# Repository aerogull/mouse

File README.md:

# beat - a mouse designed for any case
I've wanted to design my own mouse for the longest time. I've built my own keyboard, so it was just the next logical step, right? Well, the complexity from a keyboard run off a microcontroller powered by qmk, to a custom programmed mouse with a proprietary mouse sensor and a nRF52 chip, was quite the leap. This is a v1, it's not going to be light, it's not going to be very small, the side button connectors will likely be changed, and the case will not be ergonomic in any way that isn't comfortable to me. The firmware will be slower than most modern mice, and I probably won't be able to bring out the full speed of the PAW3395 sensor used (if I use ESB). But this is a testing board, and changes will be made to improve it in the future! With that, onto the specs and design!
## PCB
- nRF52840
- PAW3395
- 11mm compatible Alps scroll (w middle click)
- 4 Omron Switches (1 other switch for middle click)
- Lipo battery (500mAH)
- Dongle (nRF52840 + USBC) (COMING SOON)
- USBC charging

## Case
## Firmware
_**Warning: The PAW3395 Driver is Propiretiary, and Can Not Be Provided by Me**_ 

### BOM
|Reference|Qty|Value|DNP|Exclude from BOM|Exclude from Board|Footprint|Datasheet|
|-----|-----|-----|-----|-----|-----|-----|-----|
|A1|1|~||||custom:PAW3395||
|C1,C29,C39|	3|	4.7μF|	|	|	|	Capacitor_SMD:C_0805_2012Metric_Pad1.18x1.45mm_HandSolder|	~|
|C2,C4,C5,C13,C14,C19,C20,C21,C22,C23,C28,C31,C38|	13|	100nF|	|	|	|	Capacitor_SMD:C_0805_2012Metric_Pad1.18x1.45mm_HandSolder|	~|
|C3,C6,C8,C10,C12,C15,C16,C18,C41,C43|	10|	10μF|	|	|	|	Capacitor_SMD:C_0805_2012Metric_Pad1.18x1.45mm_HandSolder|	~|
|C7|	1|	33uF|	|	|	|	Capacitor_SMD:C_0805_2012Metric_Pad1.18x1.45mm_HandSolder|	~|
|C11,C17,C42|	3|	1μF|	|	|	|	Capacitor_SMD:C_0805_2012Metric_Pad1.18x1.45mm_HandSolder|	~|
|C24,C25,C26,C27|	4|	12pF|	|	|	|	Capacitor_SMD:C_0805_2012Metric_Pad1.18x1.45mm_HandSolder|	~|
|C30,C32|	2|	1.0μF|	|	|	|	Capacitor_SMD:C_0805_2012Metric_Pad1.18x1.45mm_HandSolder|	~|
|C33,C37|	2|	N.C.|	|	|	|	Capacitor_SMD:C_0805_2012Metric_Pad1.18x1.45mm_HandSolder|	~|
|C34|	1|	100pF|	|	|	|	Capacitor_SMD:C_0805_2012Metric_Pad1.18x1.45mm_HandSolder|	~|
|C35|	1|	0.8pF|	|	|	|	Capacitor_SMD:C_0805_2012Metric_Pad1.18x1.45mm_HandSolder|	~|
|C36|	1|	0.5pF|	|	|	|	Capacitor_SMD:C_0805_2012Metric_Pad1.18x1.45mm_HandSolder|	~|
|D3,D5|	2|	MBR1020VL|	|	|	|	Diode_SMD:D_SOD-123F|	https://www.onsemi.com/pub/Collateral/MBR1020VL-D.PDF|
|J2|	1|	JSTPH|	|	|	|	custom:JSTPH2PINSMTRIGHTANGLECONNECTOR|	~|
|J3|	1|	USB_C_Receptacle_USB2.0_14P|	|	|	|	Connector_USB:USB_C_Receptacle_Amphenol_12401548E4-2A|	https://www.usb.org/sites/default/files/documents/usb_type-c.zip|
|L1,L4|	2|	10μH|	|	|	|	Inductor_SMD:L_0805_2012Metric_Pad1.05x1.20mm_HandSolder|	~|
|L2|	1|	15nH|	|	|	|	Inductor_SMD:L_0805_2012Metric_Pad1.05x1.20mm_HandSolder|	~|
|L3|	1|	3.3nH|	|	|	|	Inductor_SMD:L_0805_2012Metric_Pad1.05x1.20mm_HandSolder|	~|
|LED1|	1|	SK6812MINI-E|	|	|	|	custom:SK6812MINIE|	http://yushakobo.jp/ds/YS-SK6812MINI-E.pdf|
|R1,R9,R10,R11,R12,R13,R20,R21|	8|	10kΩ|	|	|	|	Resistor_SMD:R_0805_2012Metric_Pad1.20x1.40mm_HandSolder|	~|
|R2|	1|	5.6Ω|	|	|	|	Resistor_SMD:R_0805_2012Metric_Pad1.20x1.40mm_HandSolder|	~|
|R3|	1|	2kΩ|	|	|	|	Resistor_SMD:R_0805_2012Metric_Pad1.20x1.40mm_HandSolder|	~|
|R4,R5,R8|	3|	100kΩ|	|	|	|	Resistor_SMD:R_0805_2012Metric_Pad1.20x1.40mm_HandSolder|	~|
|R6|	1|	5.1kΩ|	|	|	|	Resistor_SMD:R_0805_2012Metric_Pad1.20x1.40mm_HandSolder|	~|
|SW1,SW2,SW4,SW5|	4|	SW_SPST|	|	|	|	custom:SW_Tactile_SPDT_Omron_D2F|	~|
|SW3|	1|	SW_SPST|	|	|	|	Button_Switch_THT:SW_PUSH_6mm|	~|
|SW6,SW7|	2|	SW_SPST|	|	|	|	Capacitor_SMD:C_0402_1005Metric|	~|
|SW8|	1|	RotaryEncoder|	|	|	|	custom:EC10E1220503|	~|
|SW9|	1|	SW_SPST|	|	|	|	Button_Switch_SMD:SW_SPST_CK_RS282G05A3|	~|
|U2|	1|	SPX3819M5-L-3-3|	|	|	|	Package_TO_SOT_SMD:SOT-23-5|	https://www.exar.com/content/document.ashx?id=22106&languageid=1033&type=Datasheet&partnumber=SPX3819&filename=SPX3819.pdf&part=SPX3819|
|U3|	1|	MCP73831-2-OT|	|	|	|	Package_TO_SOT_SMD:SOT-23-5|	http://ww1.microchip.com/downloads/en/DeviceDoc/20001984g.pdf|
|U4|	1|	TLV70019_SOT23-5|	|	|	|	Package_TO_SOT_SMD:SOT-23-5|	http://www.ti.com/lit/ds/symlink/tlv700.pdf|
|U5|	1|	nRF52840|	|	|	|	Package_DFN_QFN:Nordic_AQFN-73-1EP_7x7mm_P0.5mm|	http://infocenter.nordicsemi.com/topic/com.nordic.infocenter.nrf52/dita/nrf52/chips/nrf52840.html|
|U6|	1|	SPX3819M5-L-5-0|	|	|	|	Package_TO_SOT_SMD:SOT-23-5|	https://www.exar.com/content/document.ashx?id=22106&languageid=1033&type=Datasheet&partnumber=SPX3819&filename=SPX3819.pdf&part=SPX3819|
|Y1|	1|	32.768 Hz|	|	|	|	custom:FC135327680KAA|	~|
|Y2|	1|	32 Hz|	|	|	|	custom:ABM8A32000MHZD2YT3|	~|

part sources for my use:

https://www.aliexpress.us/item/3256808047644394.html
https://www.aliexpress.us/item/2251832785225269.html
https://www.aliexpress.us/item/3256808439402083.html
https://www.aliexpress.us/item/3256808650485013.html

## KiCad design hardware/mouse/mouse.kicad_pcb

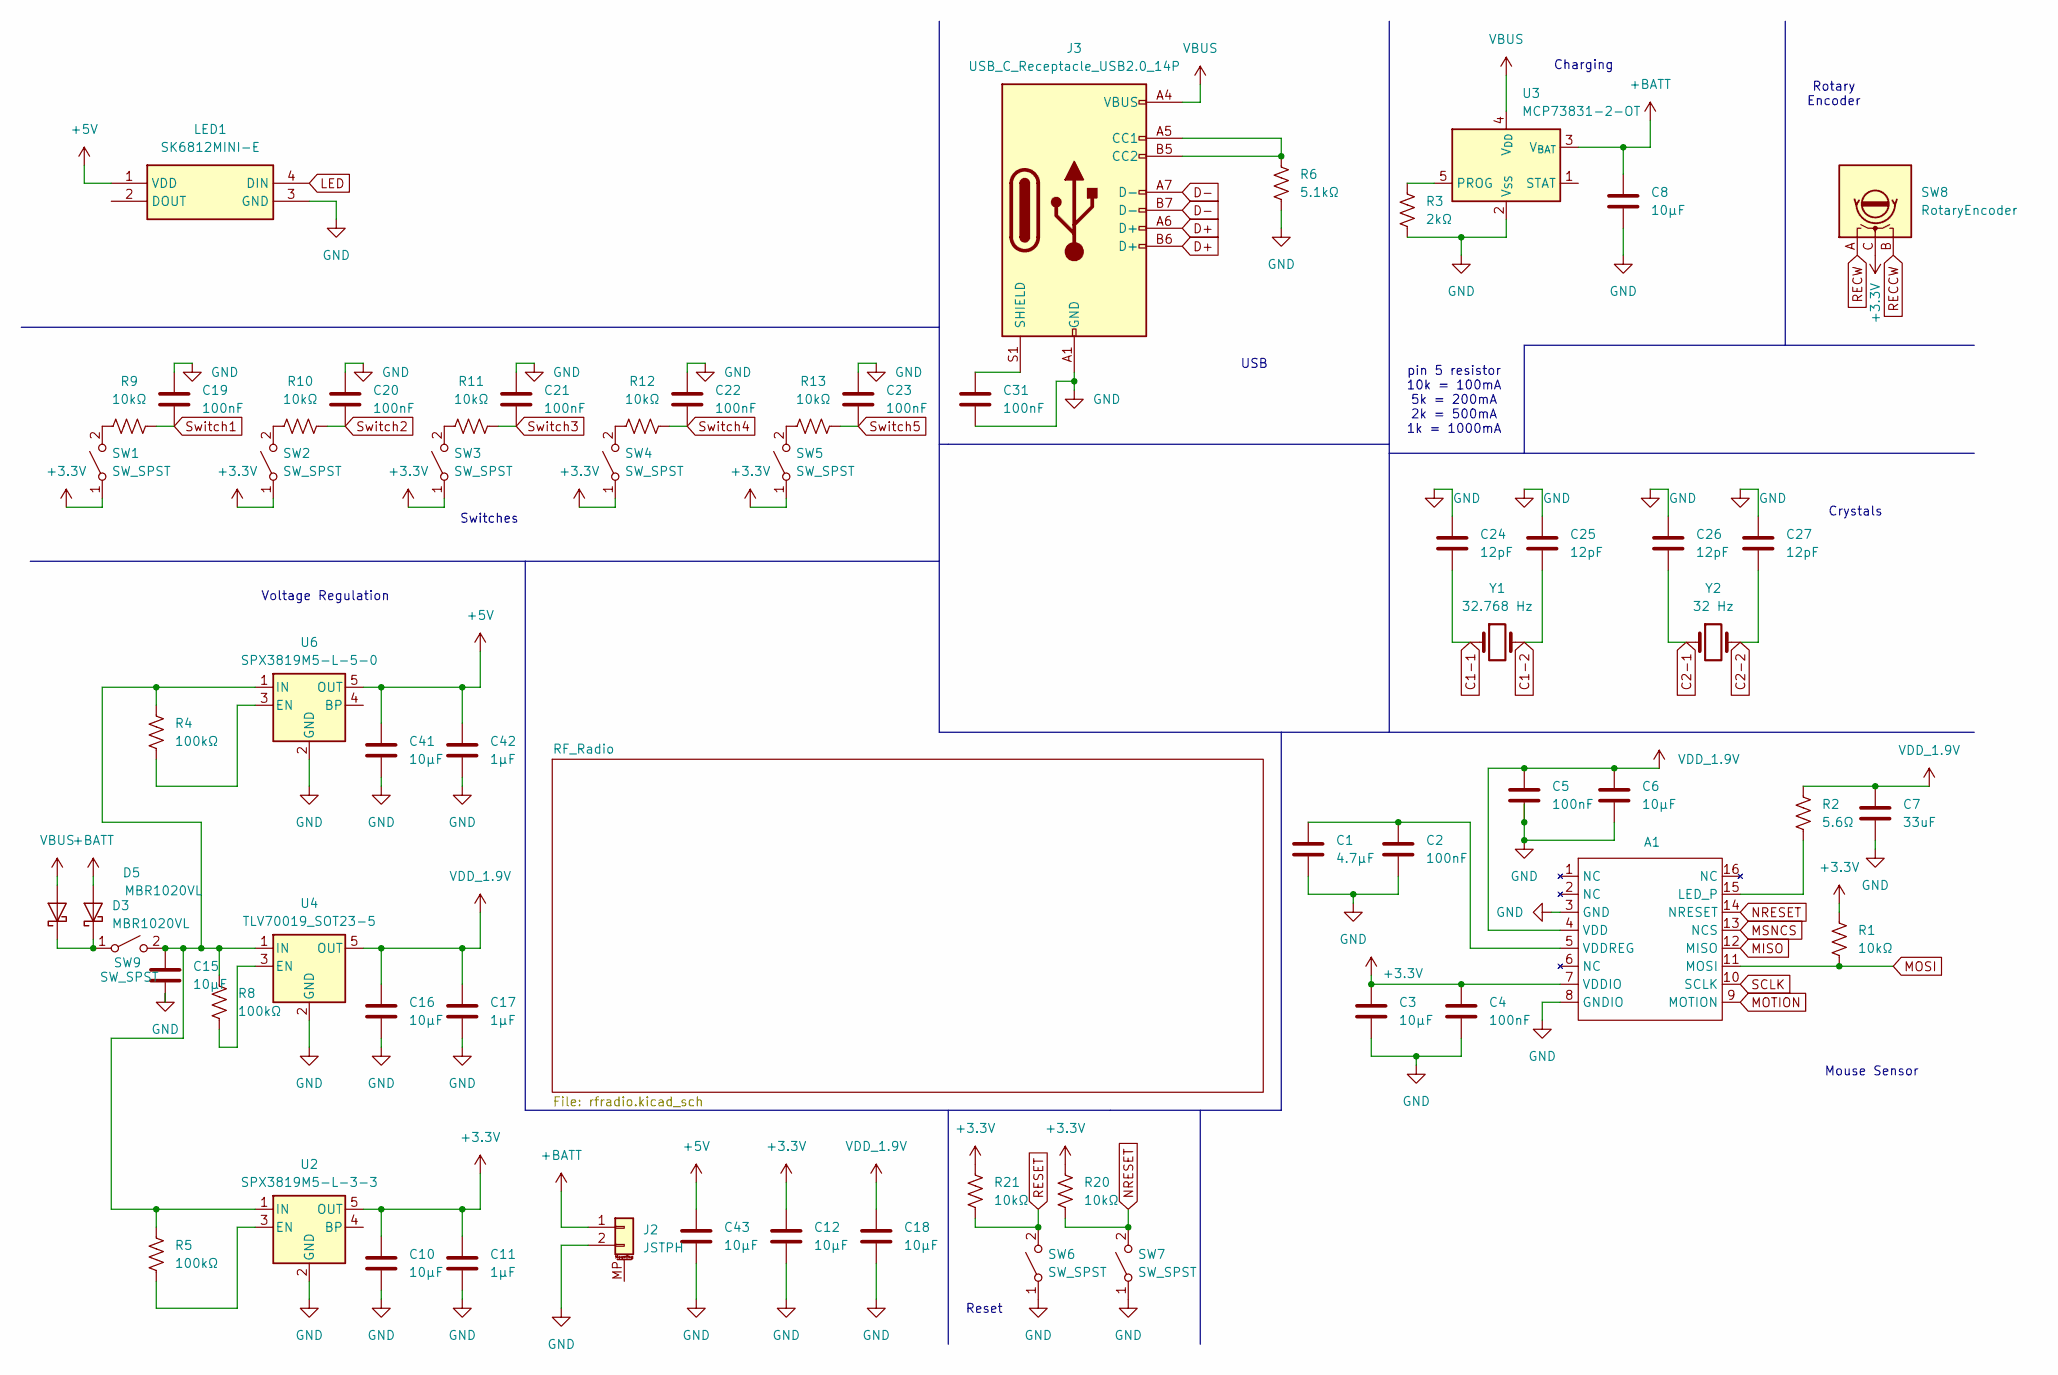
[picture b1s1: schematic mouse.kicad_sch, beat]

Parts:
A1: PAW3395
C1: 4.7μF; C_0805_2012Metric_Pad1.18x1.45mm_HandSolder
C2, C4, C5, C19, C20, C21, C22, C23, C31: 100nF; C_0805_2012Metric_Pad1.18x1.45mm_HandSolder
C3, C6, C8, C10, C12, C15, C16, C18, C41, C43: 10μF; C_0805_2012Metric_Pad1.18x1.45mm_HandSolder
C7: 33uF; C_0805_2012Metric_Pad1.18x1.45mm_HandSolder
C11, C17, C42: 1μF; C_0805_2012Metric_Pad1.18x1.45mm_HandSolder
C24, C25, C26, C27: 12pF; C_0805_2012Metric_Pad1.18x1.45mm_HandSolder
D3, D5: MBR1020VL; D_SOD-123F
J2: JSTPH; JSTPH2PINSMTRIGHTANGLECONNECTOR
J3: USB_C_Receptacle_USB2.0_14P; AMPHENOL_12401598E4_2A
LED1: SK6812MINI-E; SK6812MINIE; Manufacturer_Part_Number SK6812MINI-E
R1, R9, R10, R11, R12, R13, R20, R21: 10kΩ; R_0805_2012Metric_Pad1.20x1.40mm_HandSolder
R2: 5.6Ω; R_0805_2012Metric_Pad1.20x1.40mm_HandSolder
R3: 2kΩ; R_0805_2012Metric_Pad1.20x1.40mm_HandSolder
R4, R5, R8: 100kΩ; R_0805_2012Metric_Pad1.20x1.40mm_HandSolder
R6: 5.1kΩ; R_0805_2012Metric_Pad1.20x1.40mm_HandSolder
SW1, SW2, SW4, SW5: SW_SPST; SW_Tactile_SPDT_Omron_D2F
SW3: SW_SPST; SW_PUSH_6mm
SW6, SW7: SW_SPST; C_0402_1005Metric
SW8: RotaryEncoder; EC10E1220503
SW9: SW_SPST; SW_SPST_CK_RS282G05A3
U2: SPX3819M5-L-3-3; SOT-23-5
U3: MCP73831-2-OT; SOT-23-5
U4: TLV70019_SOT23-5; SOT-23-5
U6: SPX3819M5-L-5-0; SOT-23-5
Y1: 32.768 Hz; FC135327680KAA
Y2: 32 Hz; ABM8A32000MHZD2YT3

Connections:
+3.3V: A1.7 (VDDIO), C3.1, C4.1, C10.1, C11.1, C12.1, R1.1, R20.2, R21.2, SW1.1 (A), SW2.1 (A), SW3.1 (A), SW4.1 (A), SW5.1 (A), SW8.C, U2.5 (OUT)
+5V: C41.1, C42.1, C43.1, LED1.1 (VDD), U6.5 (OUT)
+BATT: C8.1, D3.2 (A), J2.1, U3.3 (V_{BAT}); also elsewhere on the board
C1-1: C24.2, Y1.1; also elsewhere on the board
C1-2: C25.2, Y1.2; also elsewhere on the board
C2-1: C26.2, Y2.1; also elsewhere on the board
C2-2: C27.2, Y2.2; also elsewhere on the board
D+: J3.A6 (D+), J3.B6 (D+); also elsewhere on the board
D-: J3.A7 (D-), J3.B7 (D-); also elsewhere on the board
GND: A1.3 (GND), A1.8 (GNDIO), C1.2, C2.2, C3.2, C4.2, C5.2, C6.2, C7.2, C8.2, C10.2, C11.2, C12.2, C15.2, C16.2, C17.2, C18.2, C19.1, C20.1, C21.1, C22.1, C23.1, C24.1, C25.1, C26.1, C27.1, C31.2, C41.2, C42.2, C43.2, J2.2, J3.A1 (GND), J3.A12 (GND), J3.B1 (GND), J3.B12 (GND), LED1.3 (GND), R3.1, R6.1, SW6.1 (A), SW7.1 (A), U2.2 (GND), U3.2 (V_{SS}), U4.2 (GND), U6.2 (GND); also elsewhere on the board
LED: LED1.4 (DIN); also elsewhere on the board
MISO: A1.12 (MISO); also elsewhere on the board
MOSI: A1.11 (MOSI), R1.2; also elsewhere on the board
MOTION: A1.9 (MOTION); also elsewhere on the board
MSNCS: A1.13 (NCS); also elsewhere on the board
NRESET: A1.14 (NRESET), R20.1, SW7.2 (B)
unnamed: A1.15 (LED_P), R2.2
unnamed: A1.5 (VDDREG), C1.1, C2.1
unnamed: D3.1 (K), D5.1 (K), SW9.1 (A)
unnamed: J3.A5 (CC1), J3.B5 (CC2), R6.2
unnamed: C31.1, J3.S1 (SHIELD)
unnamed: R9.1, SW1.2 (B)
unnamed: R10.1, SW2.2 (B)
unnamed: R11.1, SW3.2 (B)
unnamed: R12.1, SW4.2 (B)
unnamed: R13.1, SW5.2 (B)
unnamed: C15.1, R4.1, R5.1, R8.1, SW9.2 (B), U2.1 (IN), U4.1 (IN), U6.1 (IN)
unnamed: R5.2, U2.3 (EN)
unnamed: R3.2, U3.5 (PROG)
unnamed: R8.2, U4.3 (EN)
unnamed: R4.2, U6.3 (EN)
RECCW: SW8.B; also elsewhere on the board
RECW: SW8.A; also elsewhere on the board
RESET: R21.1, SW6.2 (B); also elsewhere on the board
SCLK: A1.10 (SCLK); also elsewhere on the board
Switch1: C19.2, R9.2; also elsewhere on the board
Switch2: C20.2, R10.2; also elsewhere on the board
Switch3: C21.2, R11.2; also elsewhere on the board
Switch4: C22.2, R12.2; also elsewhere on the board
Switch5: C23.2, R13.2; also elsewhere on the board
VBUS: D5.2 (A), J3.A4 (VBUS), J3.A9 (VBUS), J3.B4 (VBUS), J3.B9 (VBUS), U3.4 (V_{DD}); also elsewhere on the board
VDD_1.9V: A1.4 (VDD), C5.1, C6.1, C7.1, C16.1, C17.1, C18.1, R2.1, U4.5 (OUT)

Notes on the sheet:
Crystals
Mouse Sensor
Reset
Voltage Regulation
Charging
Switches
USB
Rotary Encoder
pin 5 resistor 10k = 100mA 5k = 200mA 2k = 500mA 1k = 1000mA

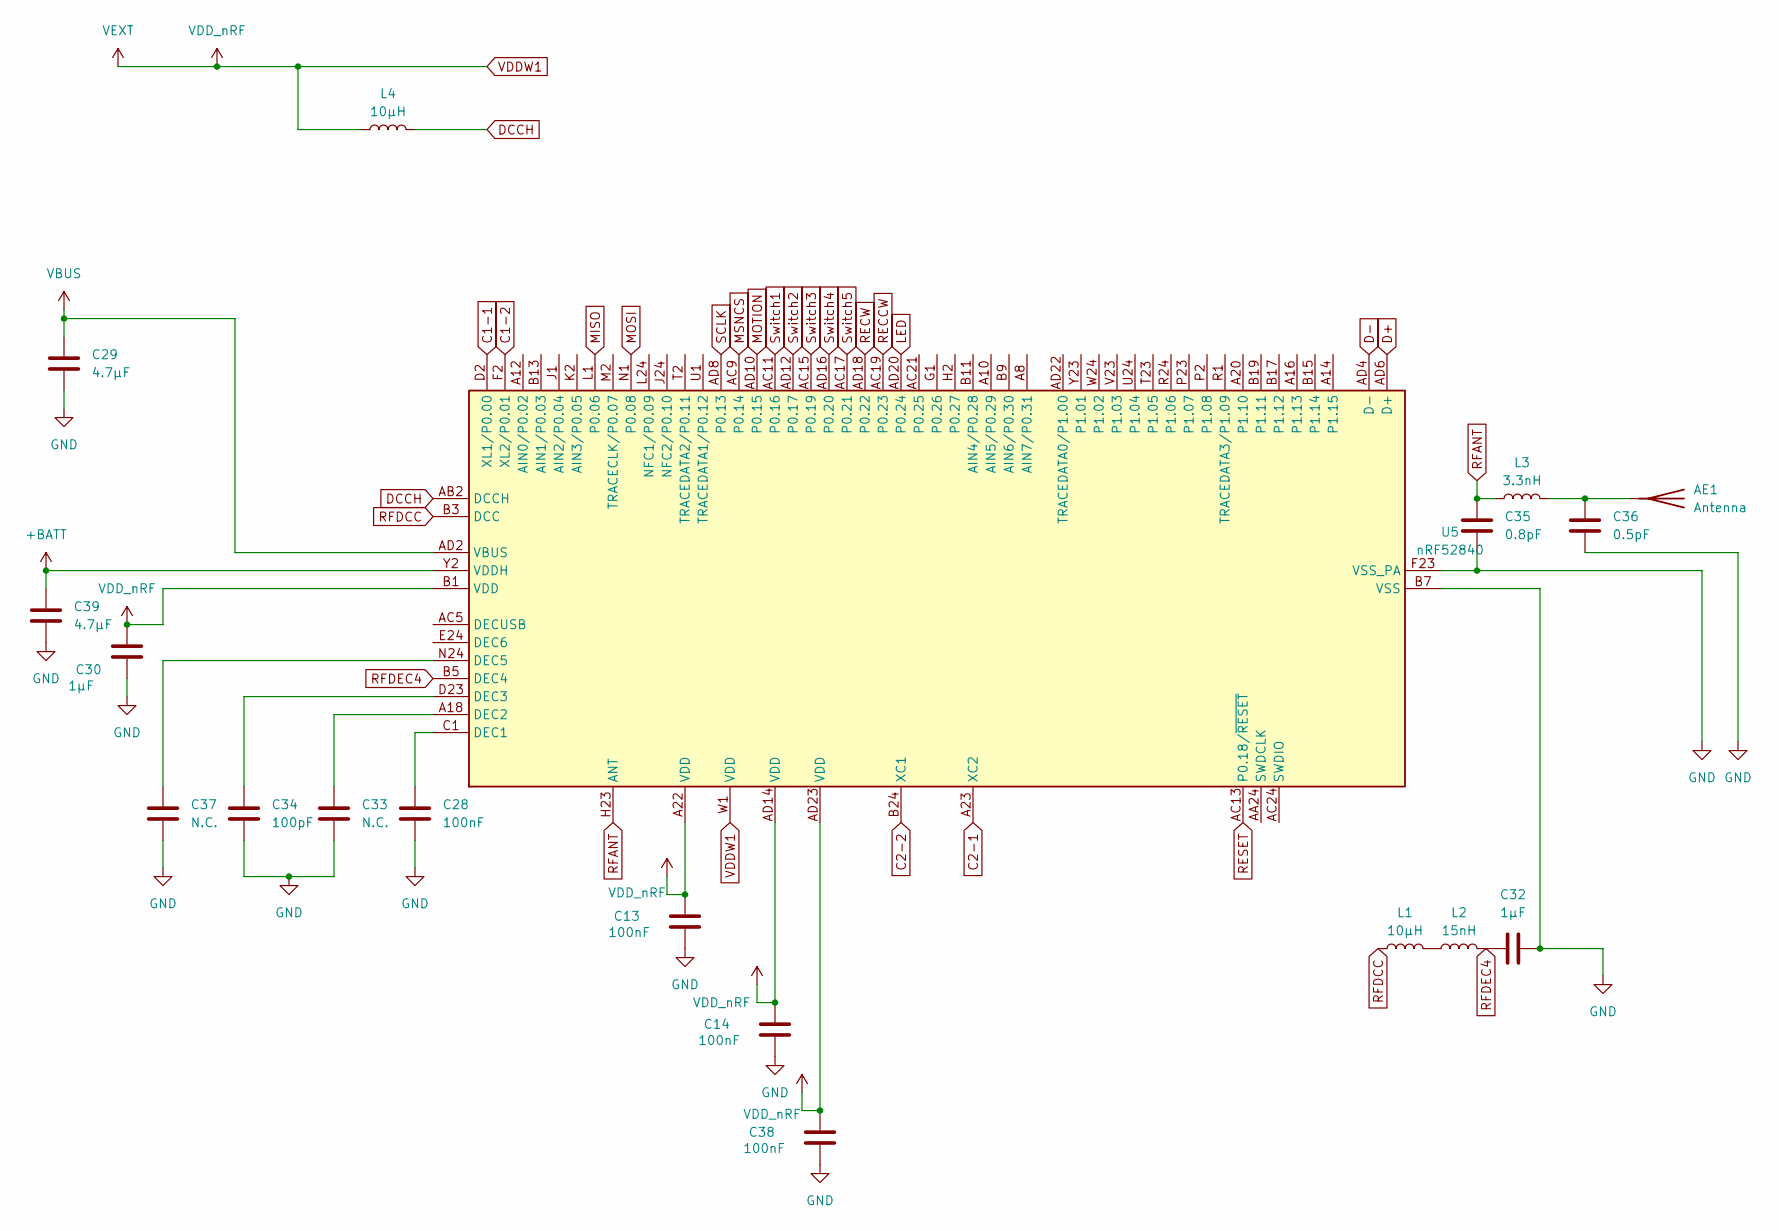
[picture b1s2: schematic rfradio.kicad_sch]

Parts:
AE1: Antenna; Texas_SWRA117D_2.4GHz_Left
C13, C14, C28, C38: 100nF; C_0805_2012Metric_Pad1.18x1.45mm_HandSolder
C29, C39: 4.7μF; C_0805_2012Metric_Pad1.18x1.45mm_HandSolder
C30, C32: 1μF; C_0805_2012Metric_Pad1.18x1.45mm_HandSolder
C33, C37: N.C.; C_0805_2012Metric_Pad1.18x1.45mm_HandSolder
C34: 100pF; C_0805_2012Metric_Pad1.18x1.45mm_HandSolder
C35: 0.8pF; C_0805_2012Metric_Pad1.18x1.45mm_HandSolder
C36: 0.5pF; C_0805_2012Metric_Pad1.18x1.45mm_HandSolder
L1, L4: 10μH; L_0805_2012Metric_Pad1.05x1.20mm_HandSolder
L2: 15nH; L_0805_2012Metric_Pad1.05x1.20mm_HandSolder
L3: 3.3nH; L_0805_2012Metric_Pad1.05x1.20mm_HandSolder
U5: nRF52840; Nordic_AQFN-73-1EP_7x7mm_P0.5mm

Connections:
+BATT: C39.1, U5.Y2 (VDDH); also elsewhere on the board
C1-1: U5.D2 (XL1/P0.00); also elsewhere on the board
C1-2: U5.F2 (XL2/P0.01); also elsewhere on the board
C2-1: U5.A23 (XC2); also elsewhere on the board
C2-2: U5.B24 (XC1); also elsewhere on the board
D+: U5.AD6 (D+); also elsewhere on the board
D-: U5.AD4 (D-); also elsewhere on the board
DCCH: L4.2, U5.AB2 (DCCH)
GND: C13.2, C14.2, C28.2, C29.2, C30.2, C32.2, C33.2, C34.2, C35.2, C36.2, C37.2, C38.2, C39.2, U5.B7 (VSS), U5.EP (VSS), U5.F23 (VSS_PA); also elsewhere on the board
LED: U5.AD20 (P0.24); also elsewhere on the board
MISO: U5.L1 (P0.06); also elsewhere on the board
MOSI: U5.N1 (P0.08); also elsewhere on the board
MOTION: U5.AD10 (P0.15); also elsewhere on the board
MSNCS: U5.AC9 (P0.14); also elsewhere on the board
unnamed: AE1.1, C36.1, L3.2
unnamed: L1.2, L2.1
unnamed: C28.1, U5.C1 (DEC1)
unnamed: C33.1, U5.A18 (DEC2)
unnamed: C34.1, U5.D23 (DEC3)
unnamed: C37.1, U5.N24 (DEC5)
RECCW: U5.AC19 (P0.23); also elsewhere on the board
RECW: U5.AD18 (P0.22); also elsewhere on the board
RESET: U5.AC13 (P0.18/~RESET); also elsewhere on the board
RFANT: C35.1, L3.1, U5.H23 (ANT)
RFDCC: L1.1, U5.B3 (DCC)
RFDEC4: C32.1, L2.2, U5.B5 (DEC4)
SCLK: U5.AD8 (P0.13); also elsewhere on the board
Switch1: U5.AC11 (P0.16); also elsewhere on the board
Switch2: U5.AD12 (P0.17); also elsewhere on the board
Switch3: U5.AC15 (P0.19); also elsewhere on the board
Switch4: U5.AD16 (P0.20); also elsewhere on the board
Switch5: U5.AC17 (P0.21); also elsewhere on the board
VBUS: C29.1, U5.AD2 (VBUS); also elsewhere on the board
VDDW1: C13.1, C14.1, C30.1, C38.1, L4.1, U5.A22 (VDD), U5.AD14 (VDD), U5.AD23 (VDD), U5.B1 (VDD), U5.W1 (VDD)

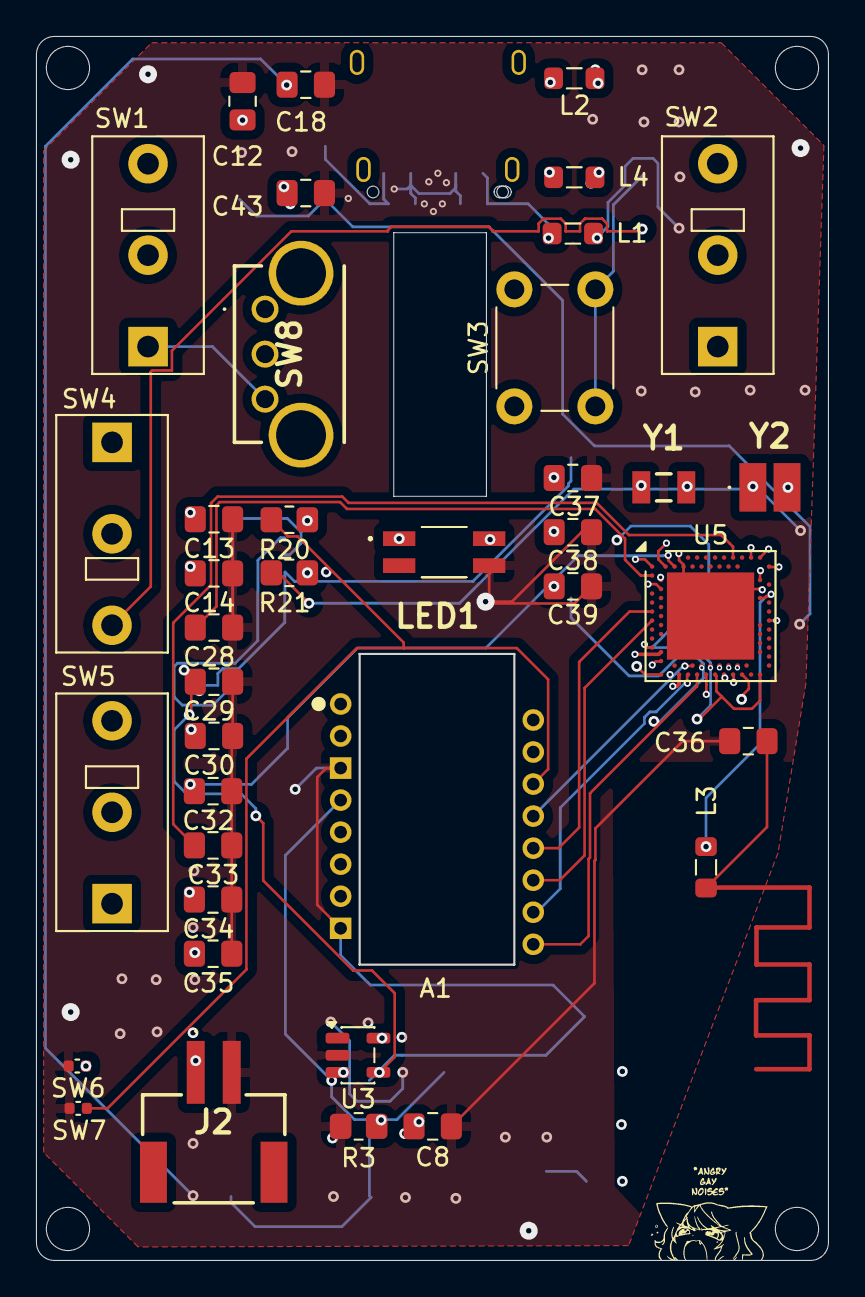
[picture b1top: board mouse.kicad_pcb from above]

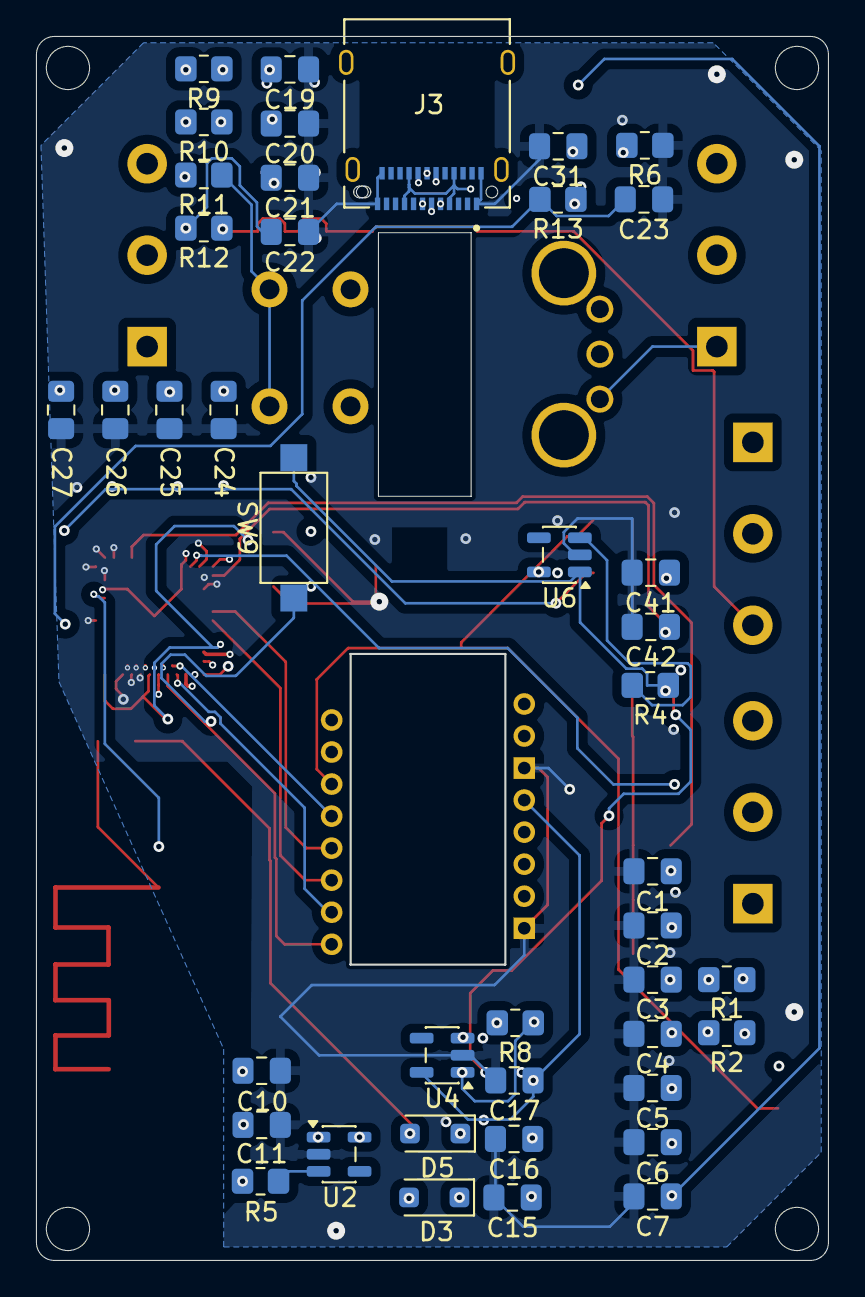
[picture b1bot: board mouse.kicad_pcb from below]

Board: 4 copper layers, 43.9 x 67.9 mm, 81 parts (42 on the bottom side), 52 nets.

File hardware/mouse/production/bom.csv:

Designator,Footprint,Quantity,Value,LCSC Part #
A1,PAW3395,1,~,
"C1, C29, C39",0805,3,4.7μF,
"C10, C12, C15, C16, C18, C3, C41, C43, C6, C8",0805,10,10μF,
"C11, C17, C30, C32, C42",0805,5,1μF,
"C13, C14, C19, C2, C20, C21, C22, C23, C28, C31, C38, C4, C5",0805,13,100nF,
"C24, C25, C26, C27",0805,4,12pF,
"C33, C37",0805,2,N.C.,
C34,0805,1,100pF,
C35,0805,1,0.8pF,
C36,0805,1,0.5pF,
C7,0805,1,33uF,
"D3, D5",D_SOD-123F,2,MBR1020VL,
J2,JSTPH2PINSMTRIGHTANGLECONNECTOR,1,JSTPH,
J3,AMPHENOL_12401598E4_2A,1,USB_C_Receptacle_USB2.0_14P,
"L1, L4",0805,2,10μH,
L2,0805,1,15nH,
L3,0805,1,3.3nH,
LED1,SK6812MINIE,1,SK6812MINI-E,
"R1, R10, R11, R12, R13, R20, R21, R9",0805,8,10kΩ,
R2,0805,1,5.6Ω,
R3,0805,1,2kΩ,
"R4, R5, R8",0805,3,100kΩ,
R6,0805,1,5.1kΩ,
"SW1, SW2, SW4, SW5",SW_Tactile_SPDT_Omron_D2F,4,SW_SPST,
SW3,SW_PUSH_6mm,1,SW_SPST,
"SW6, SW7",0402,2,SW_SPST,
SW8,EC10E1220503,1,RotaryEncoder,
SW9,SW_SPST_CK_RS282G05A3,1,SW_SPST,
U2,SOT-23-5,1,SPX3819M5-L-3-3,
U3,SOT-23-5,1,MCP73831-2-OT,
U4,SOT-23-5,1,TLV70019_SOT23-5,
U5,Nordic_AQFN-73-1EP_7x7mm_P0.5mm,1,nRF52840,
U6,SOT-23-5,1,SPX3819M5-L-5-0,
Y1,FC135327680KAA,1,32.768 Hz,
Y2,ABM8A32000MHZD2YT3,1,32 Hz,

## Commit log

2025-10-04 error checking
2025-10-13 changed bom
2025-10-13 finished the first version of the schematic
2025-11-14 forogt to fix charging
2025-11-20 fixed the led voltage and usb-c cc
2025-11-27 all pcb routing done (i got carried away)
2025-11-28 added bom to README
2025-12-10 idr what changed
